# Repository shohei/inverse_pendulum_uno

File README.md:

# Inverse pendulum shield UNO

# Changelog
Timer1(16bit) of Arduino UNO may not work with Simulink 
Should consider to use Timer0 and Timer2.

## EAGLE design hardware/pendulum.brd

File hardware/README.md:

# Inverse pendulum shield UNO

# Changelog
Timer1(16bit) of Arduino UNO may not work with Simulink 
Should consider to use Timer0 and Timer2.

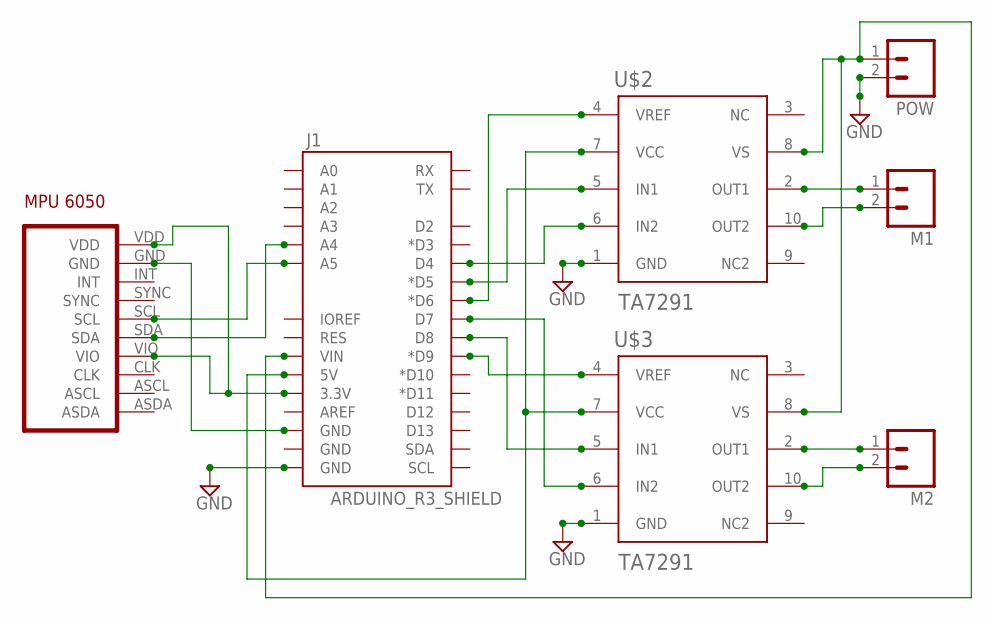
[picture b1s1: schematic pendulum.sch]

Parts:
J1: ARDUINO_R3_SHIELD; UNO_R3_SHIELD
M1, M2: M02LOCK_LONGPADS; 1X02_LOCK_LONGPADS
POW: M02LOCK_LONGPADS; 1X02_LOCK_LONGPADS
U$1: MPU6050
U$2, U$3: TA7291; HSIP10

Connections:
GND: J1.GND@0 (GND), POW.2, U$2.1 (GND), U$3.1 (GND)
unnamed: J1.A4, U$1.SDA
unnamed: J1.A5, U$1.SCL
unnamed: J1.GND@2 (GND), U$1.GND
unnamed: M1.1, U$2.2 (OUT1)
unnamed: J1.3.3V, U$1.VDD, U$1.VIO
unnamed: M1.2, U$2.10 (OUT2)
unnamed: M2.1, U$3.2 (OUT1)
unnamed: M2.2, U$3.10 (OUT2)
unnamed: J1.VIN, POW.1, U$2.8 (VS), U$3.8 (VS)
unnamed: J1.D6 (*D6), U$2.4 (VREF)
unnamed: J1.D9 (*D9), U$3.4 (VREF)
unnamed: J1.D5 (*D5), U$2.5 (IN1)
unnamed: J1.D4, U$2.6 (IN2)
unnamed: J1.D8, U$3.5 (IN1)
unnamed: J1.D7, U$3.6 (IN2)
unnamed: J1.5V, U$2.7 (VCC), U$3.7 (VCC)

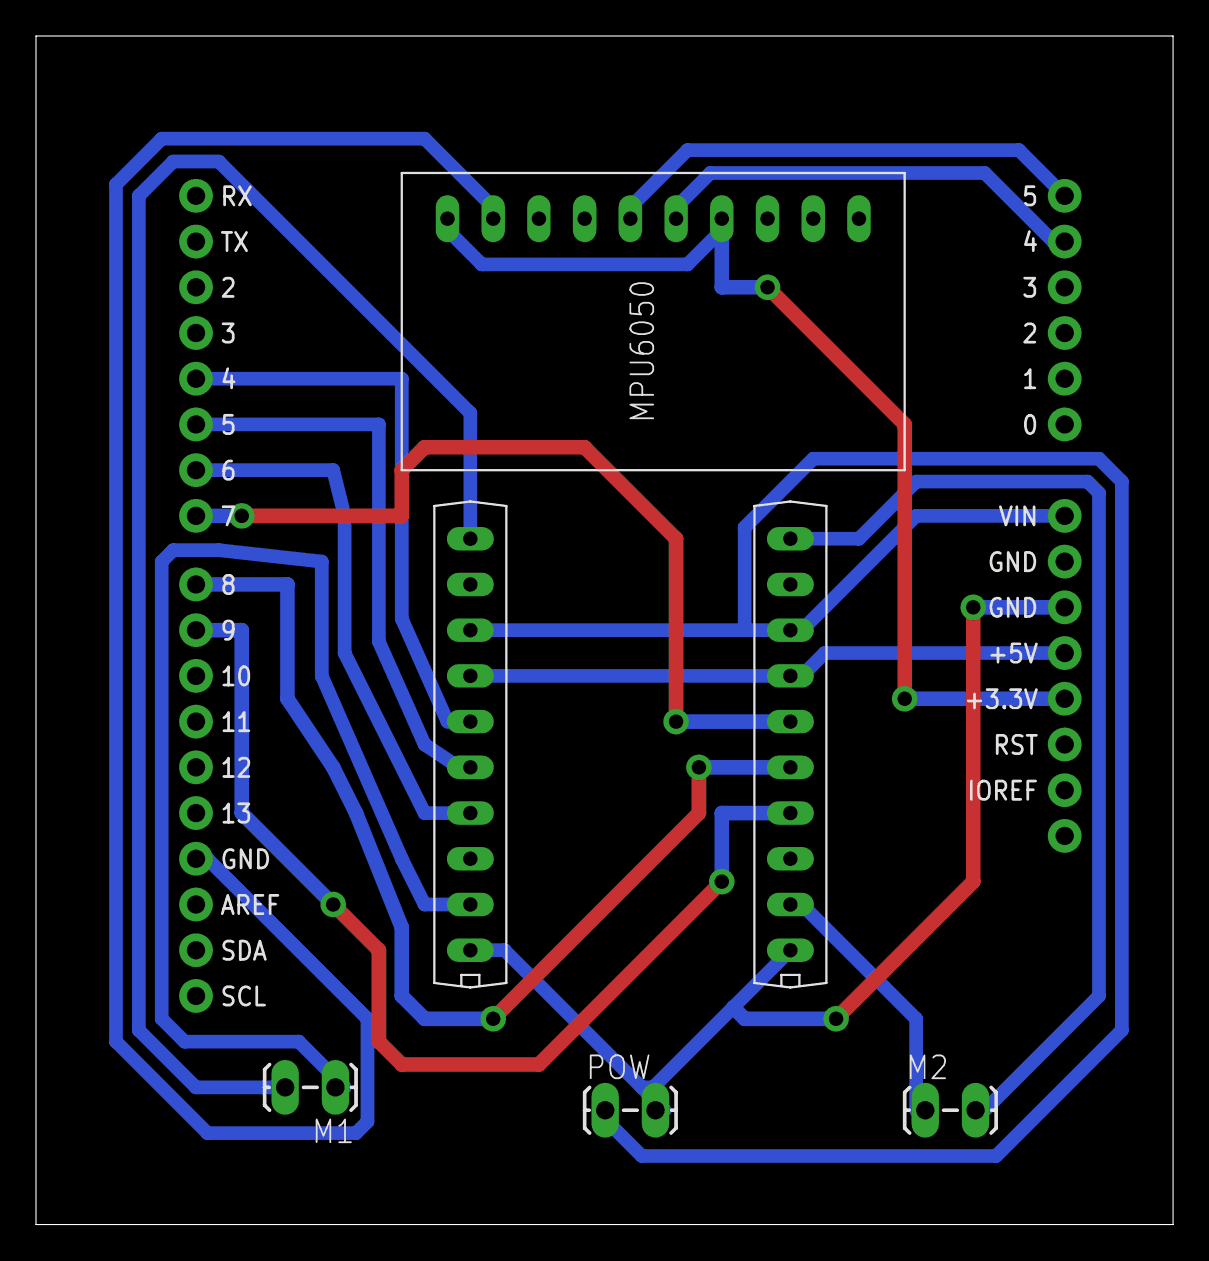
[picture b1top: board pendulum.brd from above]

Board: 2 copper layers, 63.2 x 66.0 mm, 7 parts (0 on the bottom side), 17 nets.

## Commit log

2016-12-21 add image
2017-04-05 move files

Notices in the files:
parts and their libraries:
SparkFun-Boards: Licensing: Creative Commons ShareAlike 4.0 International - https://creativecommons.org/licenses/by-sa/4.0
